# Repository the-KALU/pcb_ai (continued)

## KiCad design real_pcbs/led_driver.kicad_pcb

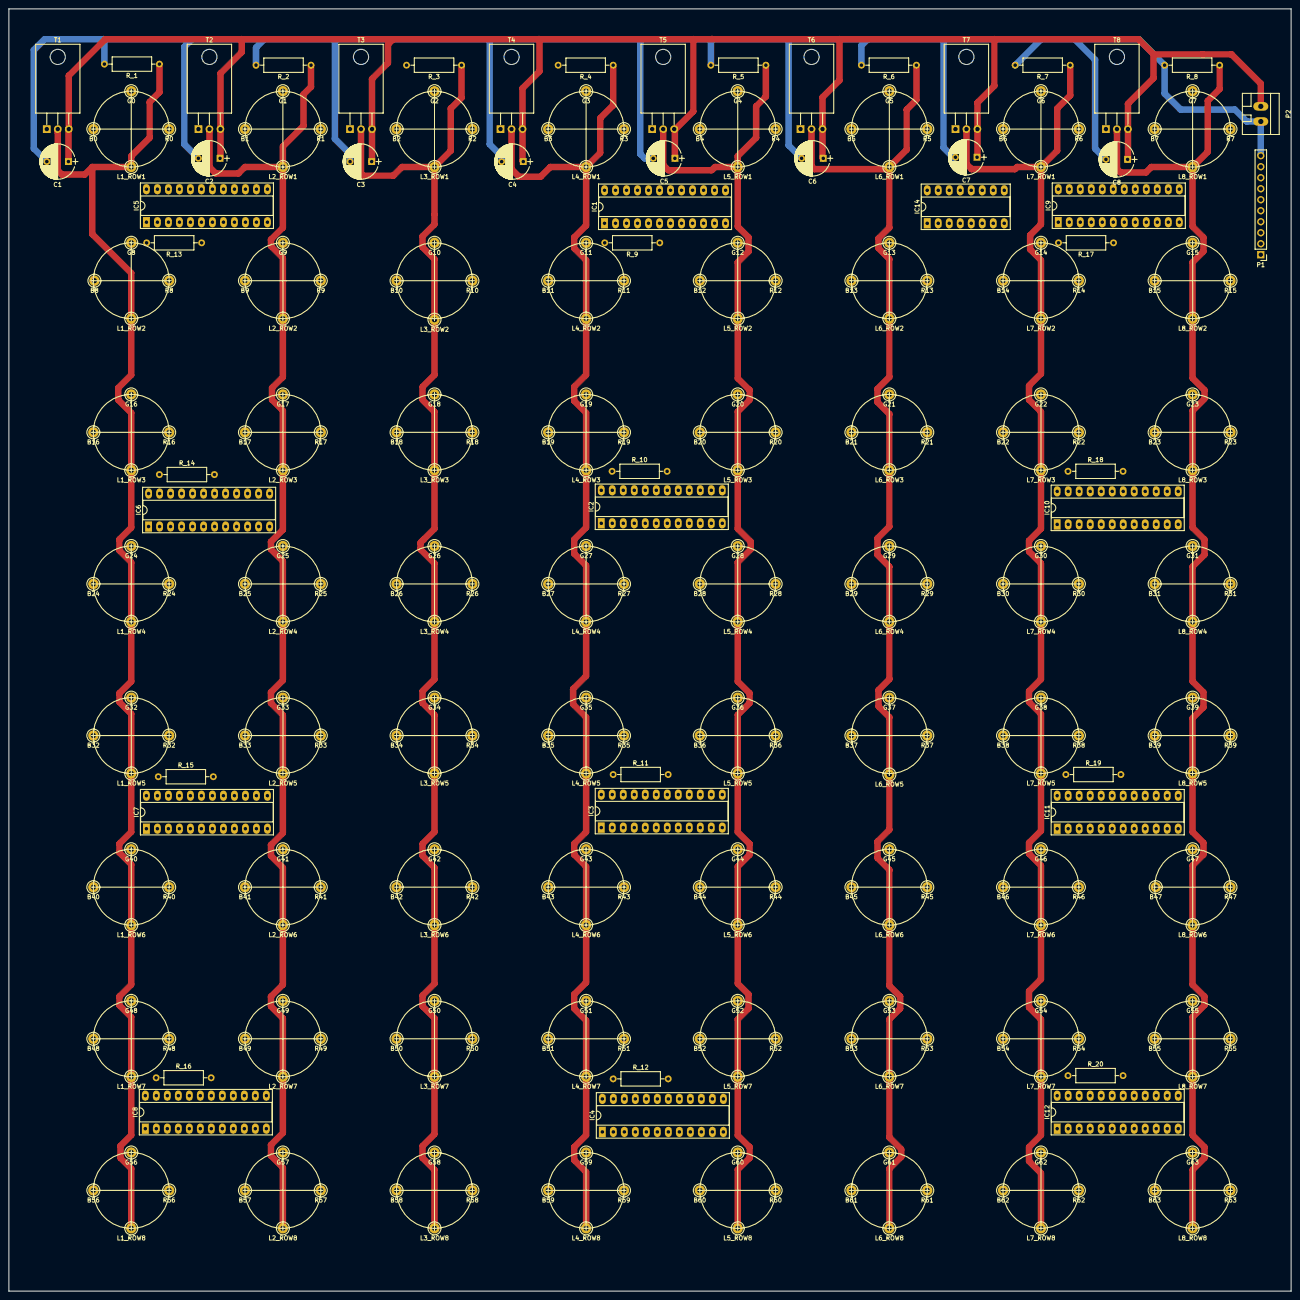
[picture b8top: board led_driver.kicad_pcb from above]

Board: 2 copper layers, 296.0 x 296.0 mm, 307 parts (0 on the bottom side), 240 nets.

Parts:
B0, B1, B2, B3, B4, B5, B6, B7, B8, B9, B10, B11, B12, B13, B14, B15, B16, B17, B18, B19, B20, B21, B22, B23, B24, B25, B26, B27, B28, B29, B30, B31, B32, B33, B34, B35, B36, B37, B38, B39, B40, B41, B42, B43, B44, B45, B46, B47, B48, B49, B50, B51, B52, B53, B54, B55, B56, B57, B58, B59, B60, B61, B62, B63: CONN_1; Pin_d1.0mm_L10.0mm_LooseFit
C1, C2, C3, C4, C5, C6, C7, C8: 1000uF; CP_Radial_D8.0mm_P5.00mm
G0, G1, G2, G3, G4, G5, G6, G7, G8, G9, G10, G11, G12, G13, G14, G15, G16, G17, G18, G19, G20, G21, G22, G23, G24, G25, G26, G27, G28, G29, G30, G31, G32, G33, G34, G35, G36, G37, G38, G39, G40, G41, G42, G43, G44, G45, G46, G47, G48, G49, G50, G51, G52, G53, G54, G55, G56, G57, G58, G59, G60, G61, G62, G63: CONN_1; Pin_d1.0mm_L10.0mm_LooseFit
IC1, IC2, IC3, IC4, IC5, IC6, IC7, IC8, IC9, IC10, IC11, IC12: DM13A; DIP-24_W7.62mm_Socket_LongPads
IC14: 74LS138; DIP-16_W7.62mm_Socket_LongPads
L1_ROW1: LAYER1; Pin_d1.0mm_L10.0mm_LooseFit
L1_ROW2, L1_ROW3, L1_ROW4, L1_ROW5, L1_ROW6, L1_ROW7, L1_ROW8, L2_ROW2, L2_ROW3, L2_ROW4, L2_ROW5, L2_ROW6, L2_ROW7, L2_ROW8, L3_ROW2, L3_ROW3, L3_ROW4, L3_ROW5, L3_ROW6, L3_ROW7, L3_ROW8, L4_ROW2, L4_ROW3, L4_ROW4, L4_ROW5, L4_ROW6, L4_ROW7, L4_ROW8, L5_ROW2, L5_ROW3, L5_ROW4, L5_ROW5, L5_ROW6, L5_ROW7, L5_ROW8, L6_ROW2, L6_ROW3, L6_ROW4, L6_ROW5, L6_ROW6, L6_ROW7, L6_ROW8, L7_ROW2, L7_ROW3, L7_ROW4, L7_ROW5, L7_ROW6, L7_ROW7, L7_ROW8, L8_ROW2, L8_ROW3, L8_ROW4, L8_ROW5, L8_ROW6, L8_ROW7, L8_ROW8: CONN_1; Pin_d1.0mm_L10.0mm_LooseFit
L2_ROW1: LAYER2; Pin_d1.0mm_L10.0mm_LooseFit
L3_ROW1: LAYER3; Pin_d1.0mm_L10.0mm_LooseFit
L4_ROW1: LAYER4; Pin_d1.0mm_L10.0mm_LooseFit
L5_ROW1: LAYER5; Pin_d1.0mm_L10.0mm_LooseFit
L6_ROW1: LAYER6; Pin_d1.0mm_L10.0mm_LooseFit
L7_ROW1: LAYER7; Pin_d1.0mm_L10.0mm_LooseFit
L8_ROW1: LAYER8; Pin_d1.0mm_L10.0mm_LooseFit
P1: CONN_10; Pin_Header_Straight_1x10_Pitch2.54mm
P2: 5V; WAGO_734_2pin_Straight_RuggedPads
R0, R1, R2, R3, R4, R5, R6, R7, R8, R9, R10, R11, R12, R13, R14, R15, R16, R17, R18, R19, R20, R21, R22, R23, R24, R25, R26, R27, R28, R29, R30, R31, R32, R33, R34, R35, R36, R37, R38, R39, R40, R41, R42, R43, R44, R45, R46, R47, R48, R49, R50, R51, R52, R53, R54, R55, R56, R57, R58, R59, R60, R61, R62, R63: CONN_1; Pin_d1.0mm_L10.0mm_LooseFit
R_1, R_2, R_3, R_4, R_5, R_6, R_7, R_8: 100; R_Axial_DIN0309_L9.0mm_D3.2mm_P12.70mm_Horizontal
R_9, R_10, R_11, R_12, R_13, R_14, R_15, R_16, R_17, R_19, R_20: 2K8; R_Axial_DIN0309_L9.0mm_D3.2mm_P12.70mm_Horizontal
R_18: 2k8; R_Axial_DIN0309_L9.0mm_D3.2mm_P12.70mm_Horizontal
T1, T2, T3, T4, T5, T6, T7, T8: MOSFET_P; TO-220-3_Horizontal

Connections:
BLUE: IC9.2, P1.3
CLOCK: IC1.3, IC2.3, IC3.3, IC4.3, IC5.3, IC6.3, IC7.3, IC8.3, IC9.3, IC10.3, IC11.3, IC12.3, P1.4
EN: IC1.21, IC2.21, IC3.21, IC4.21, IC5.21, IC6.21, IC7.21, IC8.21, IC9.21, IC10.21, IC11.21, IC12.21, IC14.4, P1.5
GND: C1.2, C2.2, C3.2, C4.2, C5.2, C6.2, C7.2, C8.2, IC1.1, IC2.1, IC3.1, IC4.1, IC5.1, IC6.1, IC7.1, IC8.1, IC9.1, IC10.1, IC11.1, IC12.1, IC14.5, IC14.8, P1.10, P2.2, R_1.2, R_2.2, R_3.2, R_4.2, R_5.2, R_6.2, R_7.2, R_8.2, R_9.2, R_10.2, R_11.2, R_12.2, R_13.2, R_14.2, R_15.2, R_16.2, R_17.2, R_18.2, R_19.2, R_20.2
GREEN: IC5.2, P1.2
LAT: IC1.4, IC2.4, IC3.4, IC4.4, IC5.4, IC6.4, IC7.4, IC8.4, IC9.4, IC10.4, IC11.4, IC12.4, P1.6
LAY1: IC14.1, P1.7
LAY2: IC14.2, P1.8
LAY3: IC14.3, P1.9
unnamed: B0.1, IC9.5
unnamed: B1.1, IC9.6
unnamed: B2.1, IC9.7
unnamed: B3.1, IC9.8
unnamed: B4.1, IC9.9
unnamed: B5.1, IC9.10
unnamed: B6.1, IC9.11
unnamed: B7.1, IC9.12
unnamed: B8.1, IC9.13
unnamed: B9.1, IC9.14
unnamed: B10.1, IC9.15
unnamed: B11.1, IC9.16
unnamed: B12.1, IC9.17
unnamed: B13.1, IC9.18
unnamed: B14.1, IC9.19
unnamed: B15.1, IC9.20
unnamed: B16.1, IC10.5
unnamed: B17.1, IC10.6
unnamed: B18.1, IC10.7
unnamed: B19.1, IC10.8
unnamed: B20.1, IC10.9
unnamed: B21.1, IC10.10
unnamed: B22.1, IC10.11
unnamed: B23.1, IC10.12
unnamed: B24.1, IC10.13
unnamed: B25.1, IC10.14
unnamed: B26.1, IC10.15
unnamed: B27.1, IC10.16
unnamed: B28.1, IC10.17
unnamed: B29.1, IC10.18
unnamed: B30.1, IC10.19
unnamed: B31.1, IC10.20
unnamed: B32.1, IC11.5
unnamed: B33.1, IC11.6
unnamed: B34.1, IC11.7
unnamed: B35.1, IC11.8
unnamed: B36.1, IC11.9
unnamed: B37.1, IC11.10
unnamed: B38.1, IC11.11
unnamed: B39.1, IC11.12
unnamed: B40.1, IC11.13
unnamed: B41.1, IC11.14
unnamed: B42.1, IC11.15
unnamed: B43.1, IC11.16
unnamed: B44.1, IC11.17
unnamed: B45.1, IC11.18
unnamed: B46.1, IC11.19
unnamed: B47.1, IC11.20
unnamed: B48.1, IC12.5
unnamed: B49.1, IC12.6
unnamed: B50.1, IC12.7
unnamed: B51.1, IC12.8
unnamed: B52.1, IC12.9
unnamed: B53.1, IC12.10
unnamed: B54.1, IC12.11
unnamed: B55.1, IC12.12
unnamed: B56.1, IC12.13
unnamed: B57.1, IC12.14
unnamed: B58.1, IC12.15
unnamed: B59.1, IC12.16
unnamed: B60.1, IC12.17
unnamed: B61.1, IC12.18
unnamed: B62.1, IC12.19
unnamed: B63.1, IC12.20
unnamed: G0.1, IC5.5
unnamed: G1.1, IC5.6
unnamed: G2.1, IC5.7
unnamed: G3.1, IC5.8
unnamed: G4.1, IC5.9
unnamed: G5.1, IC5.10
unnamed: G6.1, IC5.11
unnamed: G7.1, IC5.12
unnamed: G8.1, IC5.13
unnamed: G9.1, IC5.14
unnamed: G10.1, IC5.15
unnamed: G11.1, IC5.16
unnamed: G12.1, IC5.17
unnamed: G13.1, IC5.18
unnamed: G14.1, IC5.19
unnamed: G15.1, IC5.20
unnamed: G16.1, IC6.5
unnamed: G17.1, IC6.6
unnamed: G18.1, IC6.7
unnamed: G19.1, IC6.8
unnamed: G20.1, IC6.9
unnamed: G21.1, IC6.10
unnamed: G22.1, IC6.11
unnamed: G23.1, IC6.12
unnamed: G24.1, IC6.13
unnamed: G25.1, IC6.14
unnamed: G26.1, IC6.15
unnamed: G27.1, IC6.16
unnamed: G28.1, IC6.17
unnamed: G29.1, IC6.18
unnamed: G30.1, IC6.19
unnamed: G31.1, IC6.20
unnamed: G32.1, IC7.5
unnamed: G33.1, IC7.6
unnamed: G34.1, IC7.7
unnamed: G35.1, IC7.8
unnamed: G36.1, IC7.9
unnamed: G37.1, IC7.10
unnamed: G38.1, IC7.11
unnamed: G39.1, IC7.12
unnamed: G40.1, IC7.13
unnamed: G41.1, IC7.14
unnamed: G42.1, IC7.15
unnamed: G43.1, IC7.16
unnamed: G44.1, IC7.17
unnamed: G45.1, IC7.18
unnamed: G46.1, IC7.19
unnamed: G47.1, IC7.20
unnamed: G48.1, IC8.5
unnamed: G49.1, IC8.6
unnamed: G50.1, IC8.7
unnamed: G51.1, IC8.8
unnamed: G52.1, IC8.9
unnamed: G53.1, IC8.10
unnamed: G54.1, IC8.11
unnamed: G55.1, IC8.12
unnamed: G56.1, IC8.13
unnamed: G57.1, IC8.14
unnamed: G58.1, IC8.15
unnamed: G59.1, IC8.16
unnamed: G60.1, IC8.17
unnamed: G61.1, IC8.18
unnamed: G62.1, IC8.19
unnamed: G63.1, IC8.20
unnamed: IC1.5, R0.1
unnamed: IC1.6, R1.1
unnamed: IC1.7, R2.1
unnamed: IC1.8, R3.1
unnamed: IC1.9, R4.1
unnamed: IC1.10, R5.1
unnamed: IC1.11, R6.1
unnamed: IC1.12, R7.1
unnamed: IC1.13, R8.1
unnamed: IC1.14, R9.1
unnamed: IC1.15, R10.1
unnamed: IC1.16, R11.1
unnamed: IC1.17, R12.1
unnamed: IC1.18, R13.1
unnamed: IC1.19, R14.1
unnamed: IC1.20, R15.1
unnamed: IC1.22, IC2.2
unnamed: IC1.23, R_9.1
unnamed: IC2.5, R16.1
unnamed: IC2.6, R17.1
unnamed: IC2.7, R18.1
unnamed: IC2.8, R19.1
unnamed: IC2.9, R20.1
unnamed: IC2.10, R21.1
unnamed: IC2.11, R22.1
unnamed: IC2.12, R23.1
unnamed: IC2.13, R24.1
unnamed: IC2.14, R25.1
unnamed: IC2.15, R26.1
unnamed: IC2.16, R27.1
unnamed: IC2.17, R28.1
unnamed: IC2.18, R29.1
unnamed: IC2.19, R30.1
unnamed: IC2.20, R31.1
unnamed: IC2.22, IC3.2
unnamed: IC2.23, R_10.1
unnamed: IC3.5, R32.1
unnamed: IC3.6, R33.1
unnamed: IC3.7, R34.1
unnamed: IC3.8, R35.1
unnamed: IC3.9, R36.1
unnamed: IC3.10, R37.1
unnamed: IC3.11, R38.1
unnamed: IC3.12, R39.1
unnamed: IC3.13, R40.1
unnamed: IC3.14, R41.1
unnamed: IC3.15, R42.1
unnamed: IC3.16, R43.1
unnamed: IC3.17, R44.1
unnamed: IC3.18, R45.1
unnamed: IC3.19, R46.1
unnamed: IC3.20, R47.1
unnamed: IC3.22, IC4.2
unnamed: IC3.23, R_11.1
unnamed: IC4.5, R48.1
unnamed: IC4.6, R49.1
unnamed: IC4.7, R50.1
unnamed: IC4.8, R51.1
unnamed: IC4.9, R52.1
unnamed: IC4.10, R53.1
unnamed: IC4.11, R54.1
unnamed: IC4.12, R55.1
unnamed: IC4.13, R56.1
unnamed: IC4.14, R57.1
unnamed: IC4.15, R58.1
unnamed: IC4.16, R59.1
unnamed: IC4.17, R60.1
unnamed: IC4.18, R61.1
unnamed: IC4.19, R62.1
unnamed: IC4.20, R63.1
unnamed: IC4.23, R_12.1
unnamed: IC5.22, IC6.2
unnamed: IC5.23, R_13.1
unnamed: IC6.22, IC7.2
unnamed: IC6.23, R_14.1
unnamed: IC7.22, IC8.2
unnamed: IC7.23, R_15.1
unnamed: IC8.23, R_16.1
unnamed: IC9.23, R_17.1
unnamed: IC9.22, IC10.2
unnamed: IC10.22, IC11.2
unnamed: IC10.23, R_18.1
unnamed: IC11.22, IC12.2
unnamed: IC11.23, R_19.1
unnamed: IC12.23, R_20.1
unnamed: IC14.7, T8.1
unnamed: IC14.9, T7.1
unnamed: IC14.10, T6.1
unnamed: IC14.11, T5.1
unnamed: IC14.12, T4.1
unnamed: IC14.13, T3.1
unnamed: IC14.14, T2.1
unnamed: IC14.15, T1.1
unnamed: L1_ROW1.1, L1_ROW2.1, L1_ROW3.1, L1_ROW4.1, L1_ROW5.1, L1_ROW6.1, L1_ROW7.1, L1_ROW8.1, R_1.1, T1.2
unnamed: L2_ROW1.1, L2_ROW2.1, L2_ROW3.1, L2_ROW4.1, L2_ROW5.1, L2_ROW6.1, L2_ROW7.1, L2_ROW8.1, R_2.1, T2.2
unnamed: L3_ROW1.1, L3_ROW2.1, L3_ROW3.1, L3_ROW4.1, L3_ROW5.1, L3_ROW6.1, L3_ROW7.1, L3_ROW8.1, R_3.1, T3.2
unnamed: L4_ROW1.1, L4_ROW2.1, L4_ROW3.1, L4_ROW4.1, L4_ROW5.1, L4_ROW6.1, L4_ROW7.1, L4_ROW8.1, R_4.1, T4.2
unnamed: L5_ROW1.1, L5_ROW2.1, L5_ROW3.1, L5_ROW4.1, L5_ROW5.1, L5_ROW6.1, L5_ROW7.1, L5_ROW8.1, R_5.1, T5.2
unnamed: L6_ROW1.1, L6_ROW2.1, L6_ROW3.1, L6_ROW4.1, L6_ROW5.1, L6_ROW6.1, L6_ROW7.1, L6_ROW8.1, R_6.1, T6.2
unnamed: L7_ROW1.1, L7_ROW2.1, L7_ROW3.1, L7_ROW4.1, L7_ROW5.1, L7_ROW6.1, L7_ROW7.1, L7_ROW8.1, R_7.1, T7.2
unnamed: L8_ROW1.1, L8_ROW2.1, L8_ROW3.1, L8_ROW4.1, L8_ROW5.1, L8_ROW6.1, L8_ROW7.1, L8_ROW8.1, R_8.1, T8.2
RED: IC1.2, P1.1
VCC: C1.1, C2.1, C3.1, C4.1, C5.1, C6.1, C7.1, C8.1, IC1.24, IC2.24, IC3.24, IC4.24, IC5.24, IC6.24, IC7.24, IC8.24, IC9.24, IC10.24, IC11.24, IC12.24, IC14.6, IC14.16, P2.1, T1.3, T2.3, T3.3, T4.3, T5.3, T6.3, T7.3, T8.3

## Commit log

2025-04-12 Initial commit: project setup
2025-04-18 Second commit
2025-05-05 Third commit
2025-05-13 Fourth commit with generate_synthetic_graphs
